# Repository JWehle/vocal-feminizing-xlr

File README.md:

# vocal-feminizing-xlr
Custom XLR microphone that filters out sounds in the male vocal range.

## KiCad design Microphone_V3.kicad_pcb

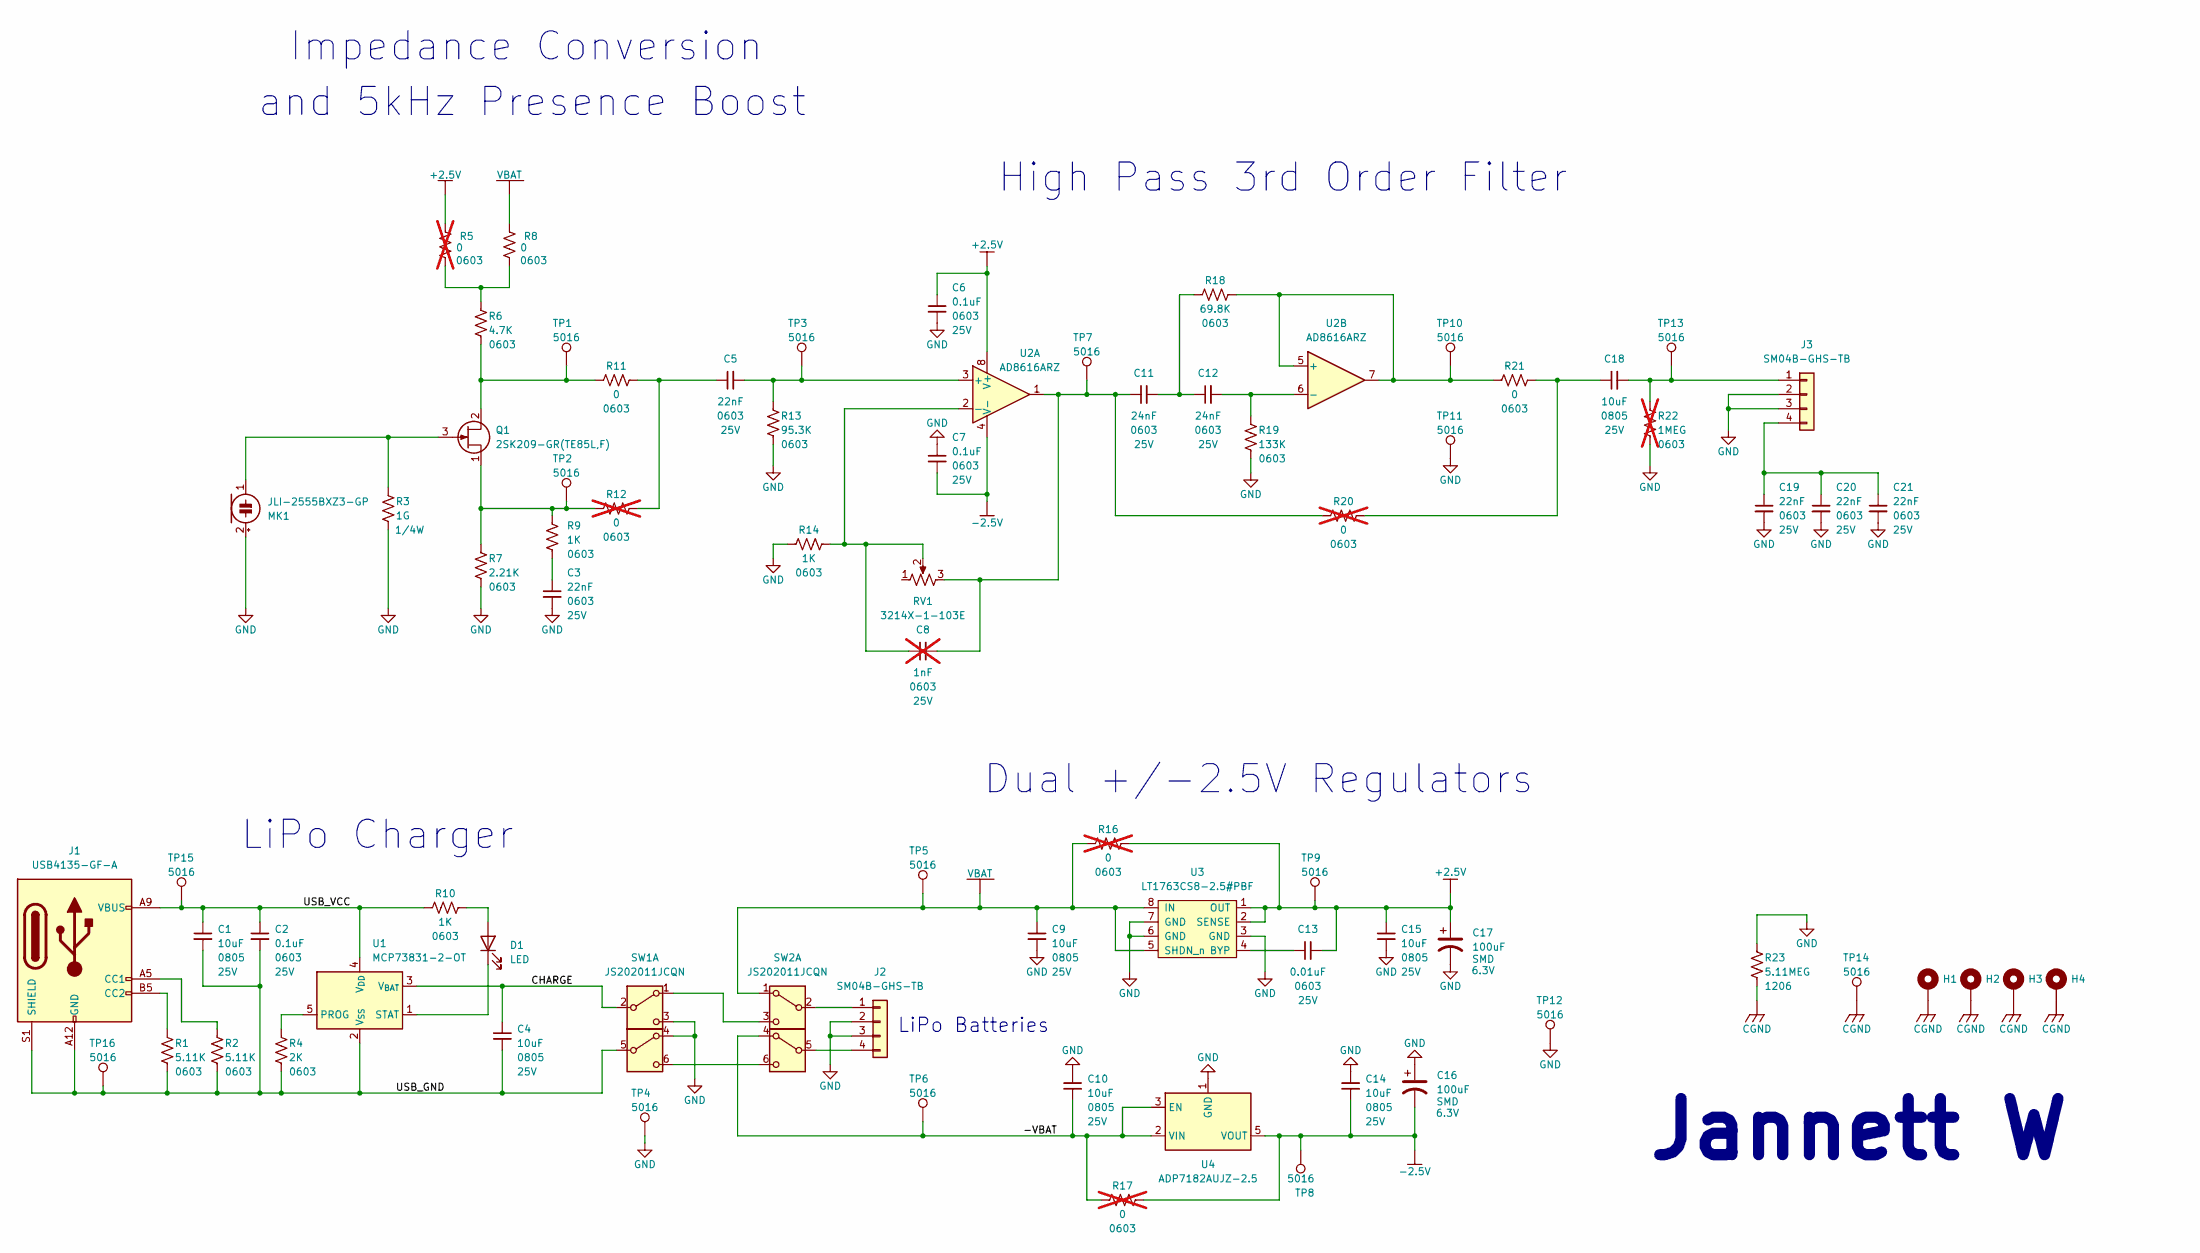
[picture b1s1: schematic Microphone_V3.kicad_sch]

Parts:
C1, C4, C9, C10, C14, C15, C18: 10uF; C_0805_2012Metric_Pad1.18x1.45mm_HandSolder; Voltage 25V
C2, C6, C7: 0.1uF; C_0603_1608Metric_Pad1.08x0.95mm_HandSolder; Voltage 25V
C3, C5, C19, C20, C21: 22nF; C_0603_1608Metric_Pad1.08x0.95mm_HandSolder; Voltage 25V
C8: 1nF; C_0603_1608Metric_Pad1.08x0.95mm_HandSolder; Voltage 25V; not fitted
C11, C12: 24nF; C_0603_1608Metric_Pad1.08x0.95mm_HandSolder; Voltage 25V
C13: 0.01uF; C_0603_1608Metric_Pad1.08x0.95mm_HandSolder; Voltage 25V
C16, C17: 100uF; CP_Elec_8x10.5; Voltage 6.3V
D1: LED; LED_0603_1608Metric_Pad1.05x0.95mm_HandSolder
H1, H2, H3, H4: MountingHole_Pad; MountingHole_3.2mm_M3_Pad_Via
J1: USB4135-GF-A; USB_C_Receptacle_GCT_USB4135-GF-A_6P_TopMnt_Horizontal
J2, J3: SM04B-GHS-TB; JST_GH_SM04B-GHS-TB_1x04-1MP_P1.25mm_Horizontal
MK1: JLI-2555BXZ3-GP
Q1: 2SK209-GR(TE85L,F); SOT-23
R1, R2: 5.11K; R_0603_1608Metric
R3: 1G; R_Axial_DIN0207_L6.3mm_D2.5mm_P10.16mm_Horizontal
R4: 2K; R_0603_1608Metric
R5, R12, R16, R17, R20: 0; R_0603_1608Metric; not fitted
R6: 4.7K; R_0603_1608Metric
R7: 2.21K; R_0603_1608Metric
R8, R11, R21: 0; R_0603_1608Metric
R9, R10, R14: 1K; R_0603_1608Metric
R13: 95.3K; R_0603_1608Metric
R18: 69.8K; R_0603_1608Metric
R19: 133K; R_0603_1608Metric
R22: 1MEG; R_0603_1608Metric; not fitted
R23: 5.11MEG; R_1206_3216Metric_Pad1.30x1.75mm_HandSolder
RV1: 3214X-1-103E; Potentiometer_Bourns_3214X_Vertical
SW1, SW2: JS202011JCQN; SW_DPDT_CK_JS202011JCQN
TP1, TP2, TP3, TP4, TP5, TP6, TP7, TP8, TP9, TP10, TP11, TP12, TP13, TP14, TP15, TP16: 5016; TestPoint_Keystone_5016_Compact
U1: MCP73831-2-OT; SOT-23-5
U2: AD8616ARZ; SOIC-8_3.9x4.9mm_P1.27mm
U3: LT1763CS8-2.5#PBF; SO-8_3.9x4.9mm_P1.27mm
U4: ADP7182AUJZ-2.5; TSOT-23-5

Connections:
+2.5V: C6.1, C13.2, C15.1, C17.1, R5.2, R16.2, TP9.1, U2.8 (V+), U3.1 (OUT), U3.2 (SENSE)
-2.5V: C7.2, C14.2, C16.2, R17.2, TP8.1, U2.4 (V-), U4.5 (VOUT)
/-VBAT: C10.2, R17.1, SW2.4 (A), TP6.1, U4.2 (VIN), U4.3 (EN)
/CHARGE: C4.1, SW1.2 (B), U1.3 (V_{BAT})
/USB_GND: C1.2, C2.2, C4.2, J1.A12 (GND), J1.B12 (GND), J1.S1 (SHIELD), R1.2, R2.2, R4.2, SW1.5 (B), TP16.1, U1.2 (V_{SS})
/USB_VCC: C1.1, C2.1, J1.A9 (VBUS), J1.B9 (VBUS), R10.1, TP15.1, U1.4 (V_{DD})
CGND: H1.1, H2.1, H3.1, H4.1, R23.2, TP14.1
GND: C3.2, C6.2, C7.1, C9.2, C10.1, C14.1, C15.2, C16.1, C17.2, C19.2, C20.2, C21.2, J2.2, J2.3, J3.2, J3.3, MK1.2 (+), R3.2, R7.2, R13.2, R14.1, R19.2, R22.2, R23.1, SW1.3 (C), SW1.4 (A), TP4.1, TP11.1, TP12.1, U3.3 (GND), U3.6 (GND), U3.7 (GND), U4.1 (GND)
unnamed: C3.1, R9.2
unnamed: C5.1, R11.2, R12.2
unnamed: C8.2, C11.1, R20.1, RV1.3, TP7.1, U2.1
unnamed: C11.2, C12.1, R18.1
unnamed: C18.1, R20.2, R21.2
unnamed: D1.2 (A), R10.2
unnamed: D1.1 (K), U1.1 (STAT)
unnamed: J1.A5 (CC1), R2.1
unnamed: J1.B5 (CC2), R1.1
unnamed: J2.1, SW2.2 (B)
unnamed: J2.4, SW2.5 (B)
unnamed: C18.2, J3.1, R22.1, TP13.1
unnamed: C19.1, C20.1, C21.1, J3.4
unnamed: MK1.1 (-), Q1.3 (G), R3.1
unnamed: Q1.2 (D), R6.2, R11.1, TP1.1
unnamed: Q1.1 (S), R7.1, R9.1, R12.1, TP2.1
unnamed: R5.1, R6.1, R8.1
unnamed: SW1.1 (A), SW2.3 (C)
unnamed: SW1.6 (C), SW2.6 (C)
unnamed: R4.1, U1.5 (PROG)
unnamed: C5.2, R13.1, TP3.1, U2.3 (+)
unnamed: C8.1, R14.2, RV1.2, U2.2 (-)
unnamed: R18.2, R21.1, TP10.1, U2.5 (+), U2.7
unnamed: C12.2, R19.1, U2.6 (-)
unnamed: C13.1, U3.4 (BYP)
VBAT: C9.1, R8.2, R16.1, SW2.1 (A), TP5.1, U3.5 (SHDN_n), U3.8 (IN)

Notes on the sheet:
and 5kHz Presence Boost
LiPo Batteries
Dual +/-2.5V Regulators
LiPo Charger
Jannett W
Impedance Conversion
High Pass 3rd Order Filter

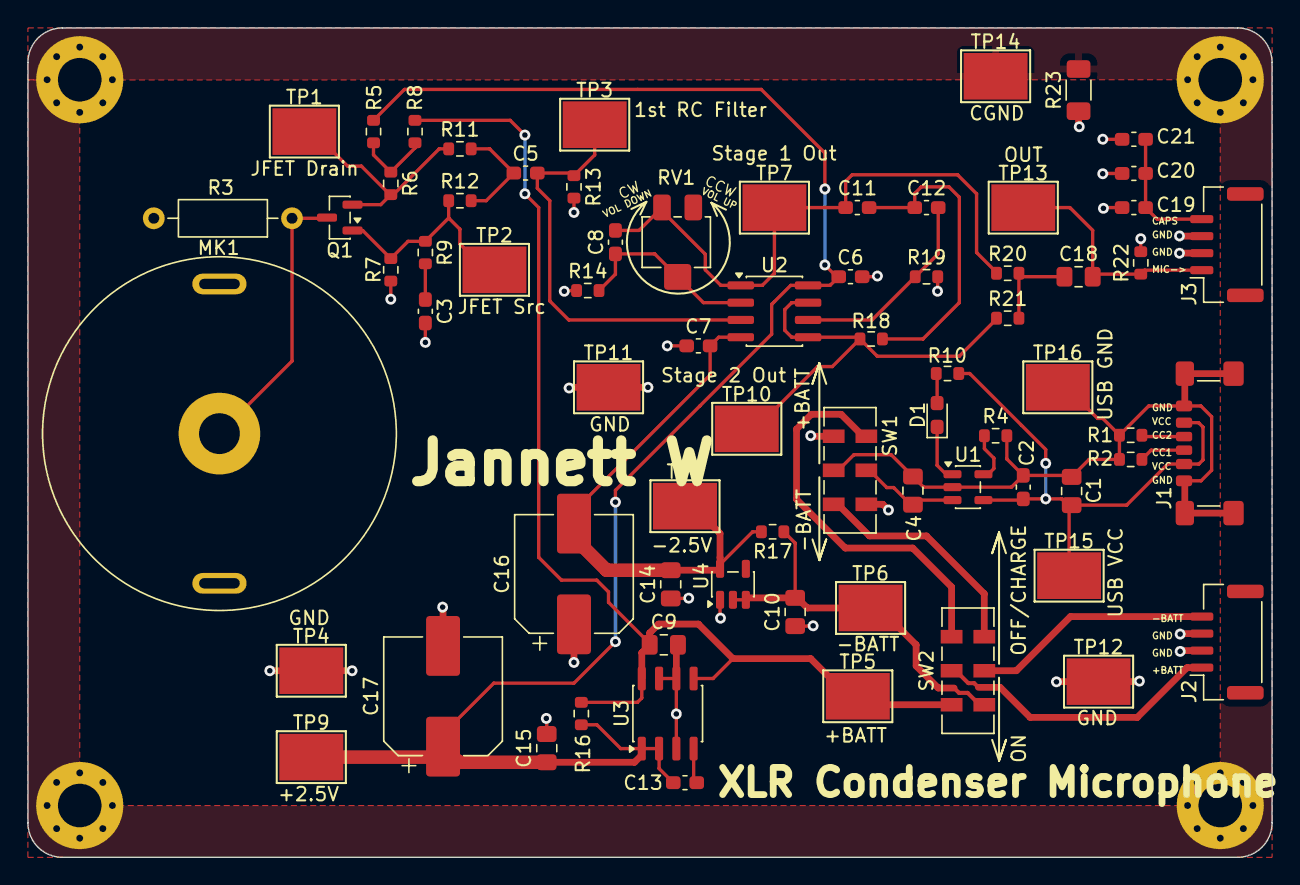
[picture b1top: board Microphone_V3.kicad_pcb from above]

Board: 2 copper layers, 91.4 x 61.0 mm, 76 parts (0 on the bottom side), 34 nets.

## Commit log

2025-01-24 layout changes
2025-01-25 layout updates
2026-02-10 schematic
2026-02-10 schematic finished
2026-02-10 layout
2026-02-17 layout finished
